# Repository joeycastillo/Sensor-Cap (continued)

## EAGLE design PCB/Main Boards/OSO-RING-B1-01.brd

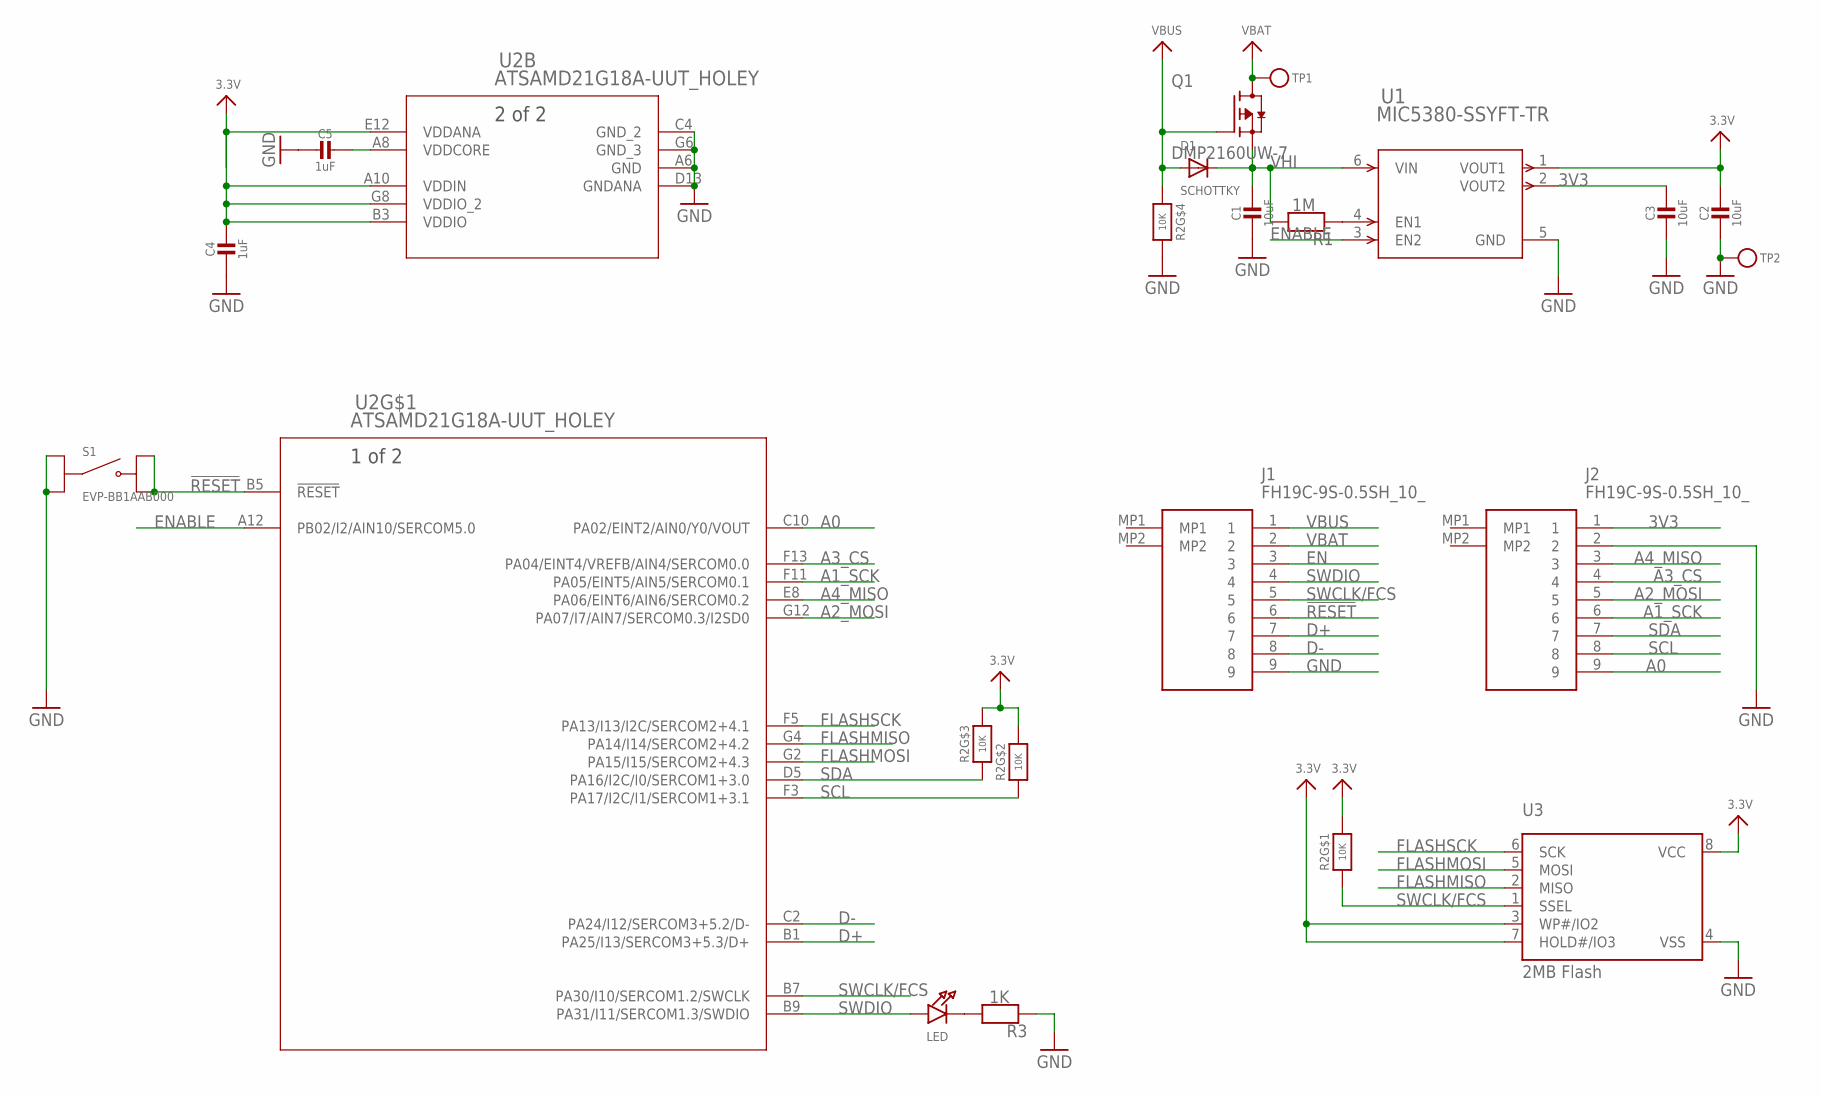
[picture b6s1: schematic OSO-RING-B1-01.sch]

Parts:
C1, C2, C3: 10uF; _0603MP
C4, C5: 1uF; _0603MP
D1: SCHOTTKY; SOD-323F
J1, J2: FH19C-9S-0.5SH_10_; FH19C9S05SH10
LED: LED0603_NOOUTLINE; CHIPLED_0603_NOOUTLINE
Q1: DMP2160UW-7; SOT65P210X110-3N
R1: 1M; _0603MP
R2: 10K; EXBV8V
R3: 1K; _0603MP
S1: EVP-BB1AAB000; SW_EVP-BB1AAB000
TP1, TP2: TESTPOINTROUND1.5MM; TESTPOINT_ROUND_1.5MM
U1: MIC5380-SSYFT-TR; TMLF-6_FT_MCH
U2: ATSAMD21G18A-UUT_HOLEY; WLCSP45_2P6X2P9_HOLEY
U3: 2MB Flash; USON8

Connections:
3.3V: C2.1, C4.1, R2.6 (2), R2.7 (2), R2.8 (2), U1.1 (VOUT1), U2.A10 (VDDIN), U2.B3 (VDDIO), U2.E12 (VDDANA), U2.G8 (VDDIO_2), U3.3 (WP#/IO2), U3.7 (HOLD#/IO3), U3.8 (VCC)
3V3: C3.1, J2.1, U1.2 (VOUT2)
!RESET: J1.6, S1.B1, S1.B2, U2.B5 (!RESET)
A0: J2.9, U2.C10 (PA02/EINT2/AIN0/Y0/VOUT)
A1_SCK: J2.6, U2.F11 (PA05/EINT5/AIN5/SERCOM0.1)
A2_MOSI: J2.5, U2.G12 (PA07/I7/AIN7/SERCOM0.3/I2SD0)
A3_CS: J2.4, U2.F13 (PA04/EINT4/VREFB/AIN4/SERCOM0.0)
A4_MISO: J2.3, U2.E8 (PA06/EINT6/AIN6/SERCOM0.2)
D+: J1.7, U2.B1 (PA25/I13/SERCOM3+5.3/D+)
D-: J1.8, U2.C2 (PA24/I12/SERCOM3+5.2/D-)
EN: J1.3, R1.1, U1.4 (EN1)
ENABLE: U1.3 (EN2), U2.A12 (PB02/I2/AIN10/SERCOM5.0)
FLASHMISO: U2.G4 (PA14/I14/SERCOM2+4.2), U3.2 (MISO)
FLASHMOSI: U2.G2 (PA15/I15/SERCOM2+4.3), U3.5 (MOSI)
FLASHSCK: U2.F5 (PA13/I13/I2C/SERCOM2+4.1), U3.6 (SCK)
GND: C1.2, C2.2, C3.2, C4.2, C5.2, J1.9, J2.2, R2.5 (2), R3.1, S1.A1, S1.A2, TP2.P$1, U1.5 (GND), U2.A6 (GND), U2.C4 (GND_2), U2.D13 (GNDANA), U2.G6 (GND_3), U3.4 (VSS)
unnamed: LED.C, R3.2
SCL: J2.8, R2.2 (1), U2.F3 (PA17/I2C/I1/SERCOM1+3.1)
SDA: J2.7, R2.3 (1), U2.D5 (PA16/I2C/I0/SERCOM1+3.0)
SWCLK/FCS: J1.5, R2.1, U2.B7 (PA30/I10/SERCOM1.2/SWCLK), U3.1 (SSEL)
SWDIO: J1.4, LED.A, U2.B9 (PA31/I11/SERCOM1.3/SWDIO)
VBAT: J1.2, Q1.3 (D), TP1.P$1
VBUS: D1.A, J1.1, Q1.1 (G), R2.4 (1)
VDDCORE: C5.1, U2.A8 (VDDCORE)
VHI: C1.1, D1.C, Q1.2 (S), R1.2, U1.6 (VIN)

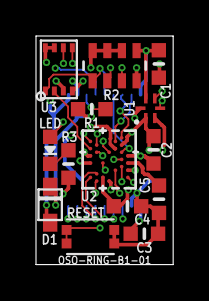
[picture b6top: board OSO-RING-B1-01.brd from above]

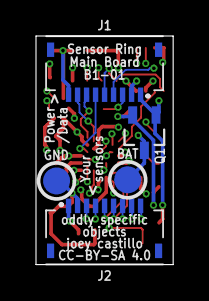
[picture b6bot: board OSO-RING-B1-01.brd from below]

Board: 6 copper layers, 7.6 x 12.7 mm, 19 parts (5 on the bottom side), 25 nets.

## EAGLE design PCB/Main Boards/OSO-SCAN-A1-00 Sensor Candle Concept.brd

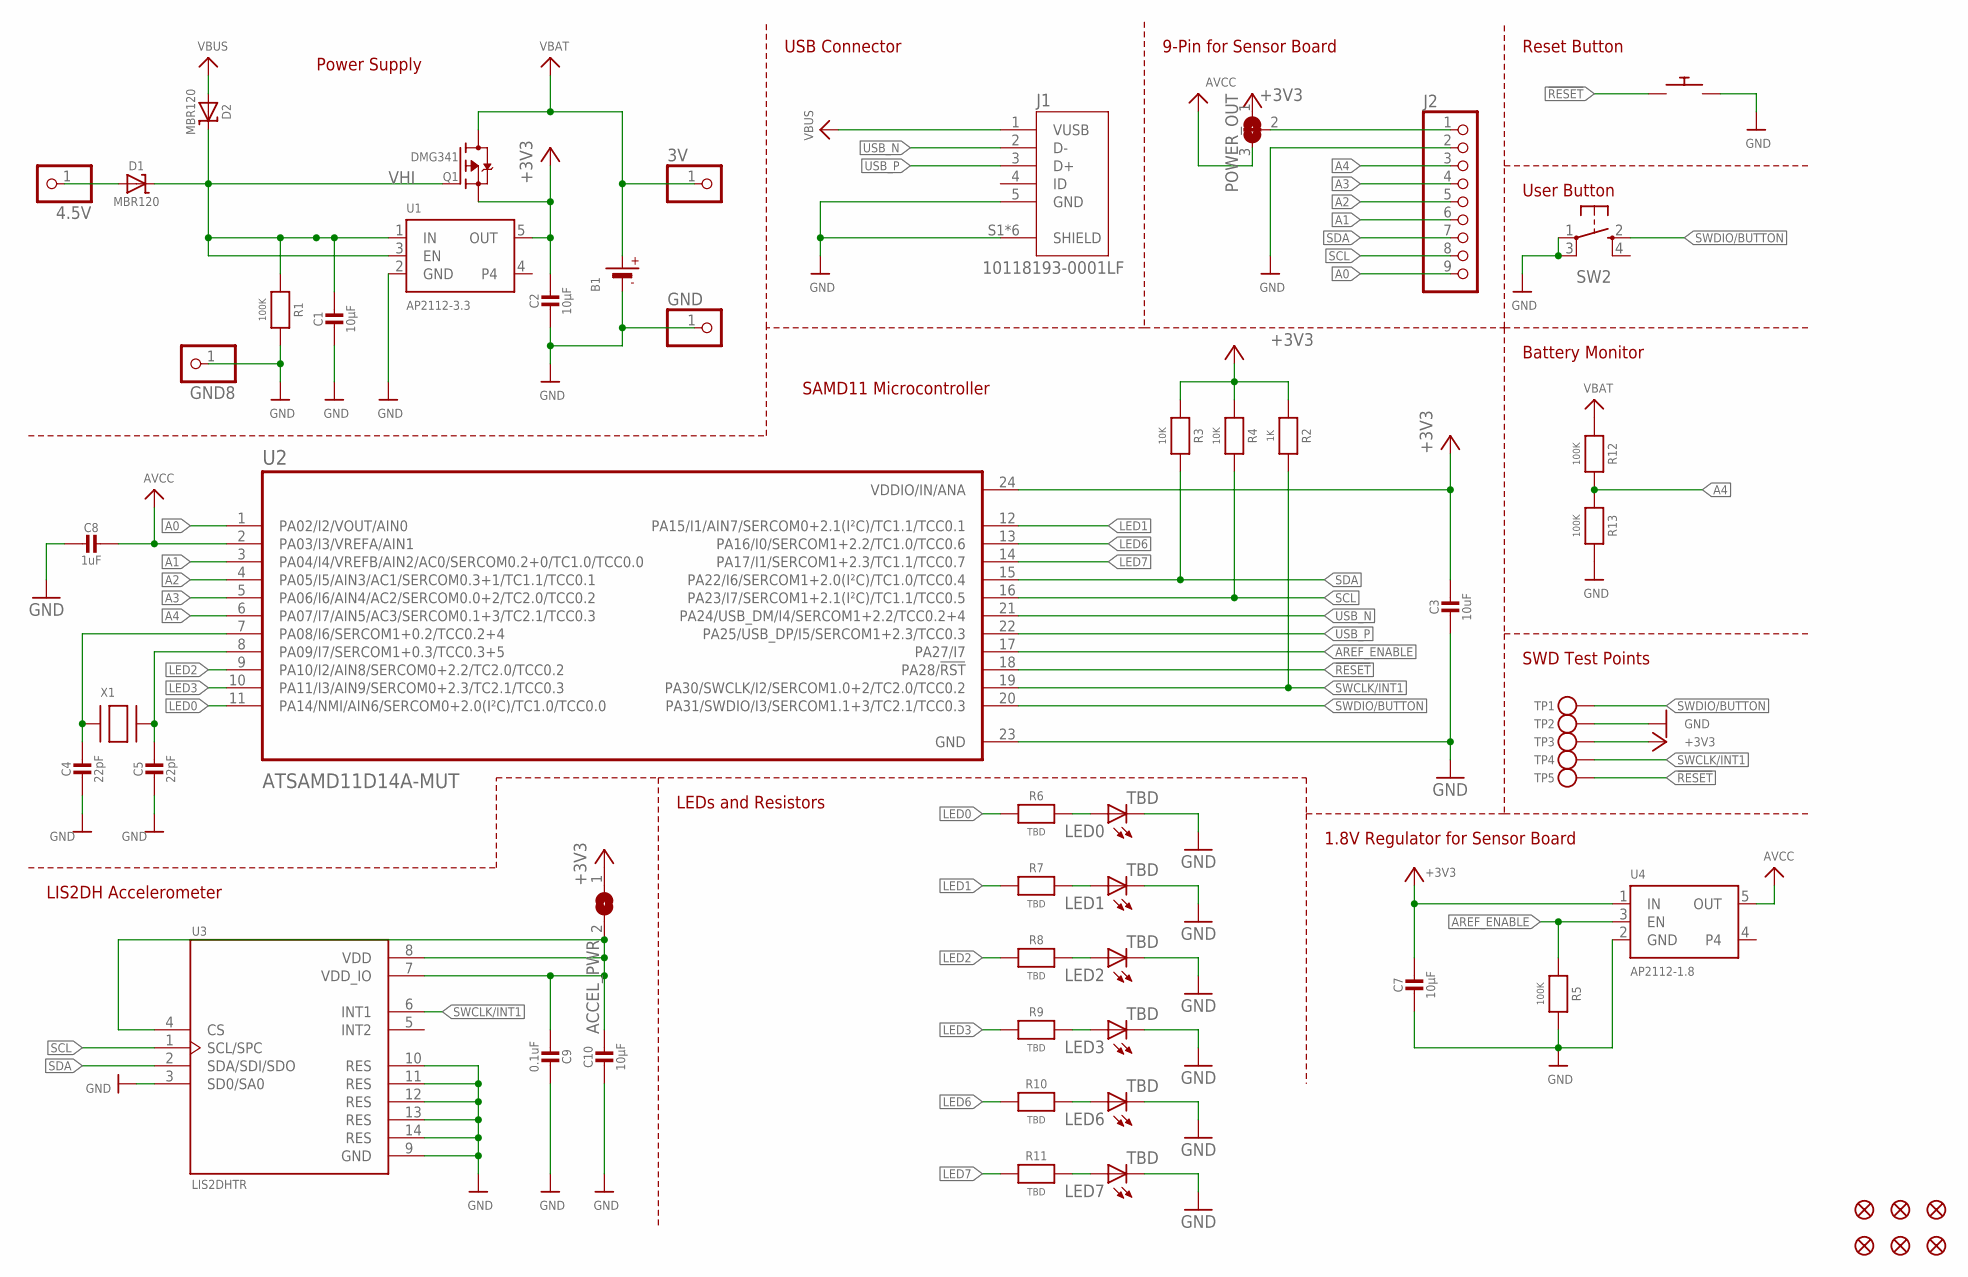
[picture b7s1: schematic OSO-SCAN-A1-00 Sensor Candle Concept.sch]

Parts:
3V, 4.5V: PINHD-1X1; 1X01
ACCEL_PWR: SOLDERJUMPERREFLOW_NOPASTE; SOLDERJUMPER_REFLOW_NOPASTE
B1: BATTERY; CR2032_SMT_BAT-HLD-BC-2003
C1, C2, C7, C10: 10µF; 0805-NO
C3: 10uF; 0805-NO
C4, C5: 22pF; 0805-NO
C8: 1uF; 0805-NO
C9: 0.1uF; 0805-NO
D1, D2: MBR120; SOD-123
FID1, FID2, FID3, FID4, FID5, FID6: FIDUCIAL_1MM
GND, GND8: PINHD-1X1; 1X01
J1: 10118193-0001LF; FCI_10118193-0001LF
J2: HEADER-1X9_JSTSH; JST_SH9
LED0, LED1, LED2, LED3, LED6, LED7: TBD; CHIP-LED0805
POWER_OUT: SOLDERJUMPER_2WAY; SOLDERJUMPER_2WAY_OPEN_NOPASTE
Q1: DMG341; SOT23-R
R1, R5, R12, R13: 100K; 0805-NO
R2: 1K; 0805-NO
R3, R4: 10K; 0805-NO
R6, R7, R8, R9, R10, R11: TBD; 0805-NO
RESET: SWITCH_PUSHBUTTONC&K_KSS; BTN_CK_KSS
SW2: SPST_TACT-KMR2; KMR2
TP1, TP2, TP3, TP4, TP5: TESTPOINTROUND2MMNO; TESTPOINT_ROUND_2MM_NO
U1: AP2112-3.3; SOT23-5
U2: ATSAMD11D14A-MUT; QFN50P400X400X90-25N
U3: LIS2DHTR; PQFN35P200X200X100-14N
U4: AP2112-1.8; SOT23-5
X1: XTAL-3.2X1.5; XTAL3215

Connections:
4.5V: 4.5V.1, D1.A
!RESET: RESET.P$1, TP5.P$1, U2.18 (PA28/!RST)
+3V3: ACCEL_PWR.1, C2.1, C3.1, C7.1, POWER_OUT.1, Q1.2 (S), R2.1, R3.1, R4.1, TP3.P$1, U1.5 (OUT), U2.24 (VDDIO/IN/ANA), U4.1 (IN)
A0: J2.9, U2.1 (PA02/I2/VOUT/AIN0)
A1: J2.6, U2.3 (PA04/I4/VREFB/AIN2/AC0/SERCOM0.2+0/TC1.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)
A2: J2.5, U2.4 (PA05/I5/AIN3/AC1/SERCOM0.3+1/TC1.1/TCC0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)
A3: J2.4, U2.5 (PA06/I6/AIN4/AC2/SERCOM0.0+2/TC2.0/TCC0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)
A4: J2.3, R12.2, R13.1, U2.6 (PA07/I7/AIN5/AC3/SERCOM0.1+3/TC2.1/TCC0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)
ACCEL_POWER: ACCEL_PWR.2, C9.2, C10.1, U3.4 (CS), U3.7 (VDD_IO), U3.8 (VDD)
AREF_ENABLE: R5.1, U2.17 (PA27/I7), U4.3 (EN)
AVCC: C8.1, POWER_OUT.3, U2.2 (PA03/I3/VREFA/AIN1), U4.5 (OUT)
GND: B1.-, C1.2, C2.2, C3.2, C4.2, C5.2, C7.2, C8.2, C9.1, C10.2, GND.1, GND8.1, J1.5 (GND), J1.S1 (SHIELD), J1.S2 (SHIELD), J1.S3 (SHIELD), J1.S4 (SHIELD), J1.S5 (SHIELD), J1.S6 (SHIELD), J2.2, LED0.C, LED1.C, LED2.C, LED3.C, LED6.C, LED7.C, R1.2, R5.2, R13.2, RESET.P$2, SW2.1, SW2.3 (P1), TP2.P$1, U1.2 (GND), U2.23 (GND), U3.3 (SD0/SA0), U3.9 (GND), U3.10 (RES), U3.11 (RES), U3.12 (RES), U3.13 (RES), U3.14 (RES), U4.2 (GND)
LED0: R6.1, U2.11 (PA14/NMI/AIN6/SERCOM0+2.0(I²C)/TC1.0/TC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)
LED1: R7.1, U2.12 (PA15/I1/AIN7/SERCOM0+2.1(I²C)/TC1.1/TCC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)
LED2: R8.1, U2.9 (PA10/I2/AIN8/SERCOM0+2.2/TC2.0/TCC0.2)
LED3: R9.1, U2.10 (PA11/I3/AIN9/SERCOM0+2.3/TC2.1/TCC0.3)
LED6: R10.1, U2.13 (PA16/I0/SERCOM1+2.2/TC1.0/TCC0.6)
LED7: R11.1, U2.14 (PA17/I1/SERCOM1+2.3/TC1.1/TCC0.7)
unnamed: LED1.A, R7.2
unnamed: LED2.A, R8.2
unnamed: LED0.A, R6.2
unnamed: LED3.A, R9.2
unnamed: LED6.A, R10.2
unnamed: LED7.A, R11.2
POWER_OUT: J2.1, POWER_OUT.2
SCL: J2.8, R4.2, U2.16 (PA23/I7/SERCOM1+2.1(I²C)/TC1.1/TCC0.5), U3.1 (SCL/SPC)
SDA: J2.7, R3.2, U2.15 (PA22/I6/SERCOM1+2.0(I²C)/TC1.0/TCC0.4), U3.2 (SDA/SDI/SDO)
SWCLK/INT1: R2.2, TP4.P$1, U2.19 (PA30/SWCLK/I2/SERCOM1.0+2/TC2.0/TCC0.2), U3.6 (INT1)
SWDIO/BUTTON: SW2.2 (S), TP1.P$1, U2.20 (PA31/SWDIO/I3/SERCOM1.1+3/TC2.1/TCC0.3)
USB_N: J1.2 (D-), U2.21 (PA24/USB_DM/I4/SERCOM1+2.2/TCC0.2+4)
USB_P: J1.3 (D+), U2.22 (PA25/USB_DP/I5/SERCOM1+2.3/TCC0.3)
VBAT: 3V.1, B1.+$1 (+), B1.+$2 (+), Q1.3 (D), R12.1
VBUS: D2.A, J1.1 (VUSB)
VHI: C1.1, D1.C, D2.C, Q1.1 (G), R1.1, U1.1 (IN), U1.3 (EN)
XIN32: C4.1, U2.7 (PA08/I6/SERCOM1+0.2/TCC0.2+4), X1.P$1
XOUT32: C5.1, U2.8 (PA09/I7/SERCOM1+0.3/TCC0.3+5), X1.P$2

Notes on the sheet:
LEDs and Resistors
LIS2DH Accelerometer
SAMD11 Microcontroller
Power Supply
USB Connector
9-Pin for Sensor Board
Reset Button
User Button
Battery Monitor
SWD Test Points
1.8V Regulator for Sensor Board

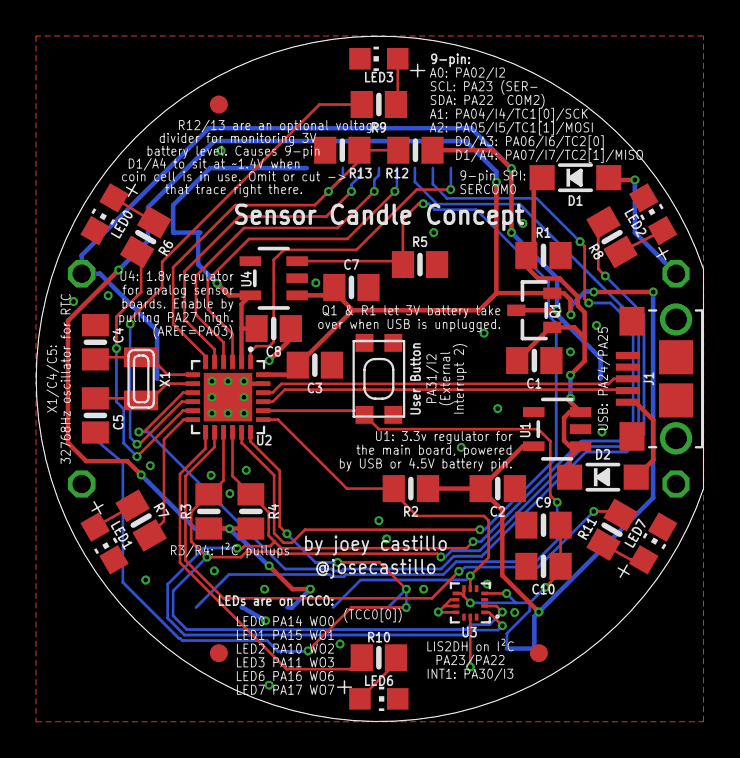
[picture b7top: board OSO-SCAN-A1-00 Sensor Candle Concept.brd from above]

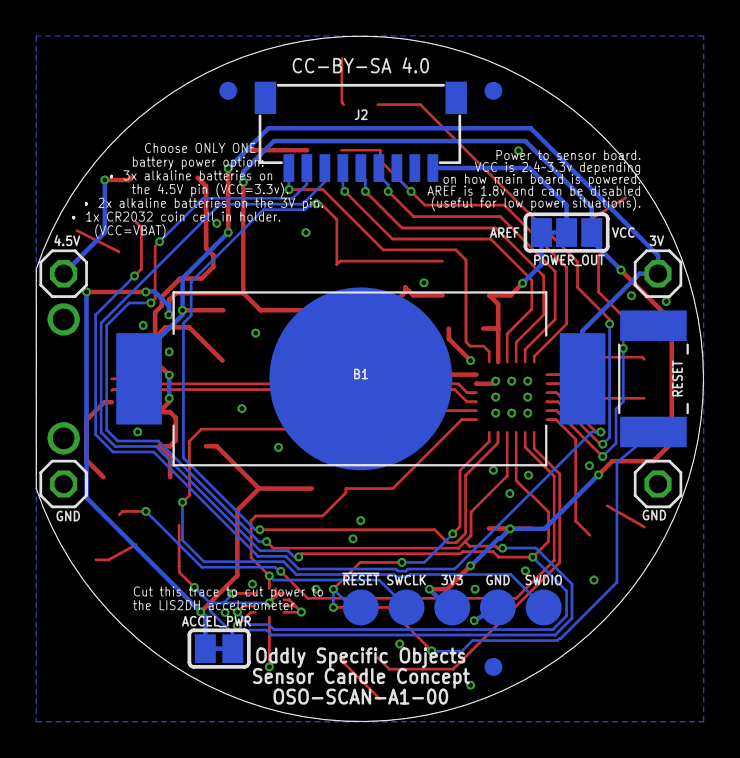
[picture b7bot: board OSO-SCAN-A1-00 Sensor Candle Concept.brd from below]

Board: 2 copper layers, 37.1 x 38.1 mm, 58 parts (17 on the bottom side), 36 nets.
